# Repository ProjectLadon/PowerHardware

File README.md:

# PowerHardware
Solar panel MPPT/battery charger/power combiner hardware

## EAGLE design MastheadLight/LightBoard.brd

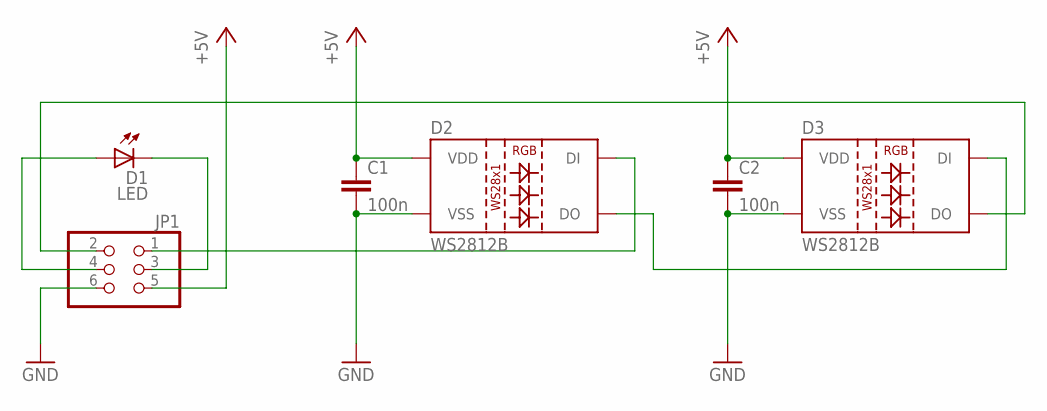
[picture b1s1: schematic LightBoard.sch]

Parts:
C1, C2: 100n; C0603
D1: LED; LM561C
D2, D3: WS2812B
JP1: PINHD-2X3_2.54-SMD-90°; 2X03SMD/90

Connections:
+5V: C1.1, C2.1, D2.1 (VDD), D3.1 (VDD), JP1.5
GND: C1.2, C2.2, D2.3 (VSS), D3.3 (VSS), JP1.6
unnamed: D2.2 (DO), D3.4 (DI)
unnamed: D2.4 (DI), JP1.1
unnamed: D3.2 (DO), JP1.2
unnamed: D1.A1 (A), D1.A2 (A), D1.A3 (A), JP1.4
unnamed: D1.C1 (C), D1.C2 (C), D1.C3 (C), JP1.3

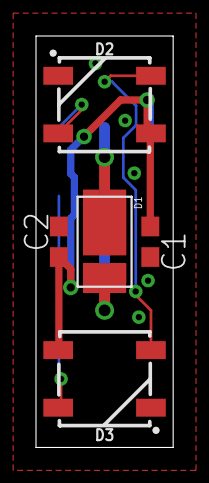
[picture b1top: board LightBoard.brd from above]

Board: 2 copper layers, 7.6 x 22.9 mm, 6 parts (1 on the bottom side), 7 nets.

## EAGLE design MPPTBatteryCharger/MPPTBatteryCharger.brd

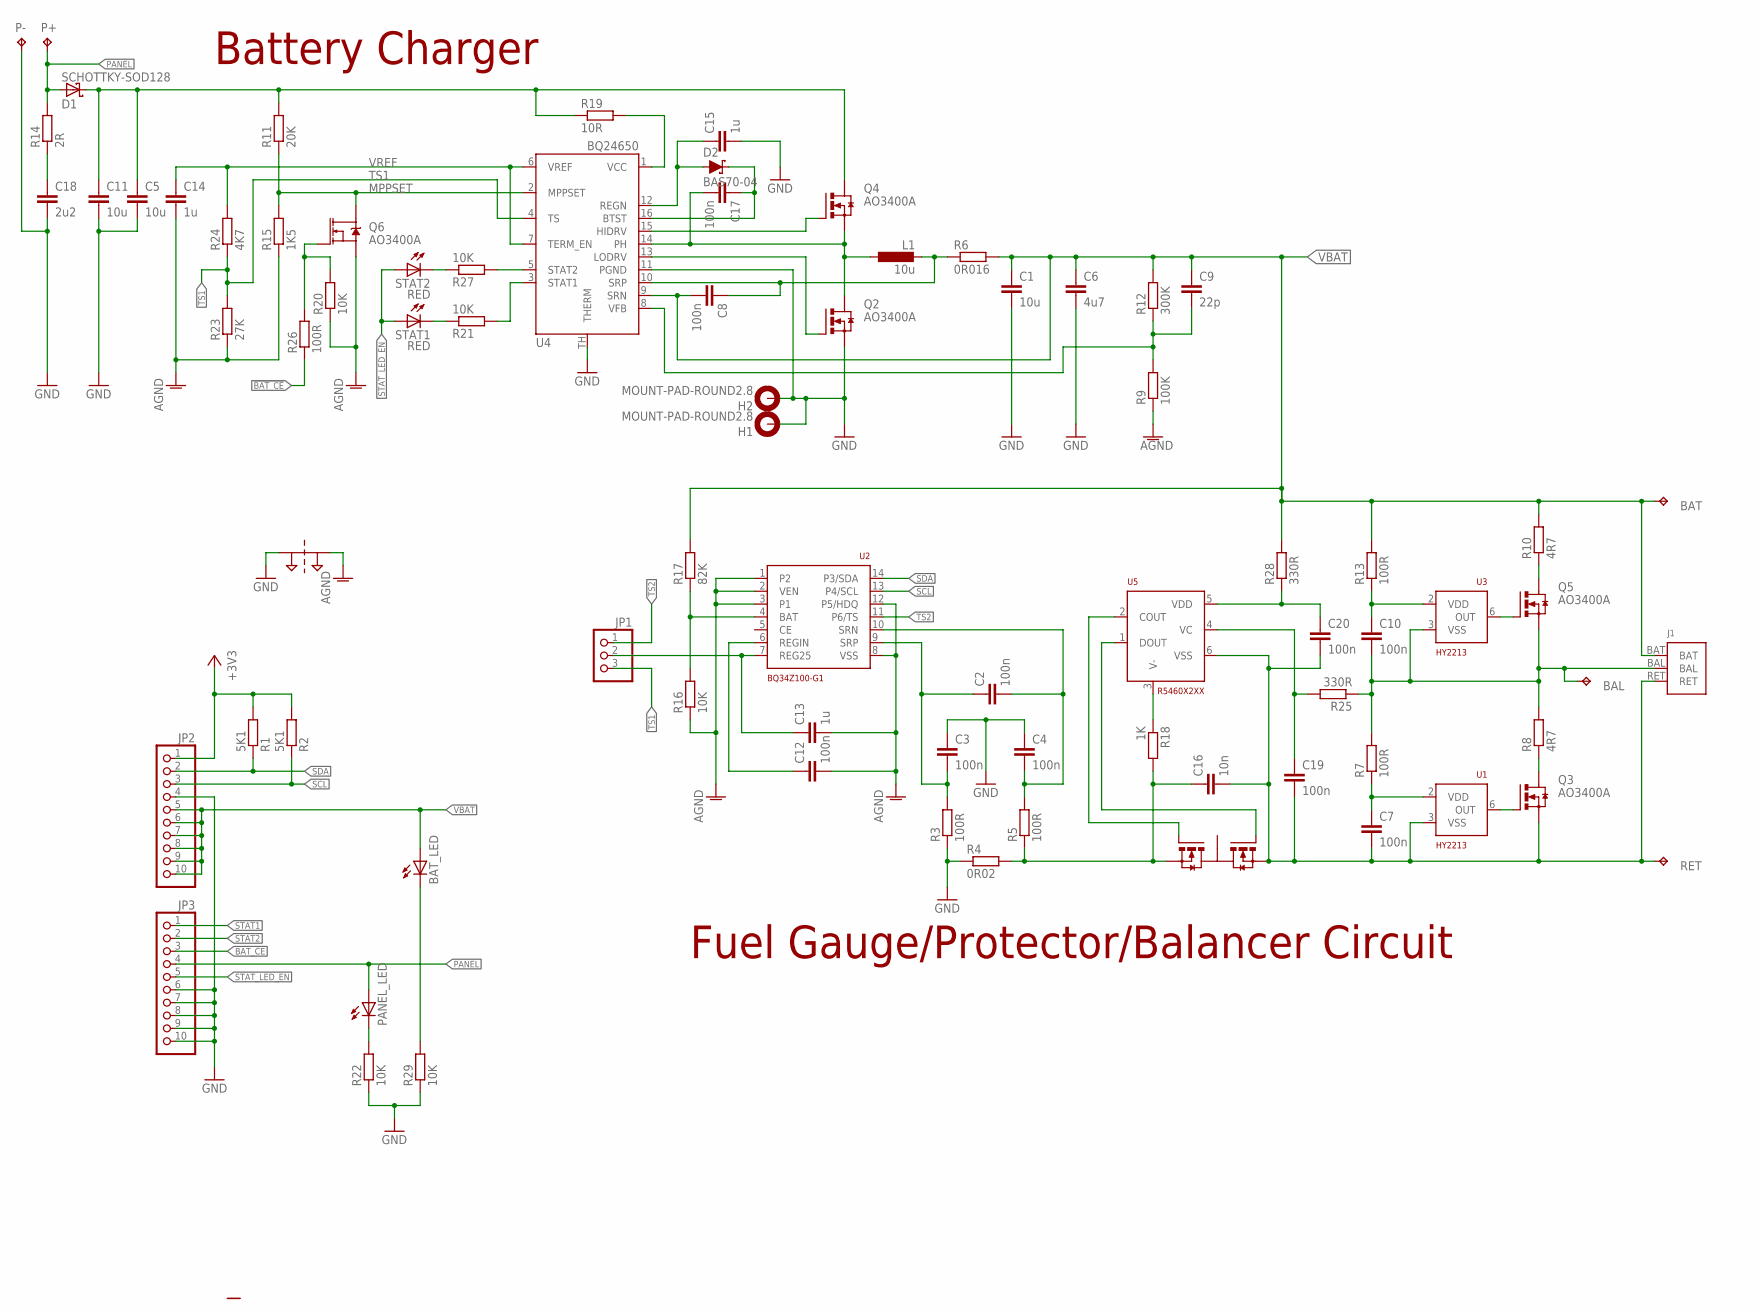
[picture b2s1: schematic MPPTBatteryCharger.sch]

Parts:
BAL: TPPAD1-13Y; P1-13Y
BAT: TPPAD1-13Y; P1-13Y
BAT_LED: LEDCHIP-LED0603; CHIP-LED0603
C1, C5, C11: 10u; C1206
C2, C3, C4, C7, C8, C10, C12, C17, C19, C20: 100n; C0402
C6: 4u7; C1206
C9: 22p; C0402
C13, C14, C15: 1u; C0402
C16: 10n; C0402
C18: 2u2; C0603
D1: SCHOTTKY-SOD128; SOD-128
D2: BAS70-04; SOT23-3
H1, H2: MOUNT-PAD-ROUND2.8; 2,8-PAD
J1: 2S-BATTERYSMD; JST-XH3-SMD
JP1: PINHD-1X3; 1X03
JP2, JP3: PINHD-1X10; 1X10
L1: 10u; MWSA1205
P+: TPPAD1-13Y; P1-13Y
P-: TPPAD1-13Y; P1-13Y
PANEL_LED: LEDCHIP-LED0603; CHIP-LED0603
Q1: FS8205; SOT23-6L
Q2, Q3, Q4, Q5: AO3400A; SOT23
Q6: AO3400A; SOT23-3
R1, R2: 5K1; R0402
R3, R5, R7, R13, R26: 100R; R0402
R4: 0R02; R1206
R6: 0R016; R1206
R8, R10: 4R7; R1206
R9: 100K; R0402
R11: 20K; R0402
R12: 300K; R0402
R14: 2R; R1206
R15: 1K5; R0402
R16: 10K; R0603
R17: 82K; R0603
R18: 1K; R0402
R19: 10R; R0402
R20, R21, R22, R27, R29: 10K; R0402
R23: 27K; R0402
R24: 4K7; R0402
R25, R28: 330R; R0402
RET: TPPAD1-13Y; P1-13Y
STAT1, STAT2: RED; CHIP-LED0603
SUPPLY1: 2PT_GND_TIE
U1, U3: HY2213; SOT23-6L; MFG_PN HY2213-BB3A; LCSC_PN C113632
U2: BQ34Z100-G1; TSSOP14; MFG_PN BQ34Z100PWR-G1; LCSC_PN C91302
U4: BQ24650; QFN16
U5: R5460X2XX; SOT23-6L; LCSC_PN C259719

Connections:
!BAT_CE!: JP3.3, R26.1
+3V3: JP2.1, R1.2, R2.2
AGND: C12.2, C13.2, C14.2, Q6.2 (S), R9.1, R15.1, R16.1, R20.1, R23.1, SUPPLY1.P$2, U2.1 (P2), U2.2 (VEN), U2.3 (P1), U2.8 (VSS), U2.12 (P5/HDQ)
BAL: BAL.TP, C10.2, J1.BAL, Q5.2 (S), R7.2, R8.2, R25.1, U3.3 (VSS)
GND: C1.2, C3.1, C4.1, C5.2, C6.2, C11.2, C15.2, C18.2, H1.B2,8, H2.B2,8, JP2.4, JP3.6, JP3.7, JP3.8, JP3.9, JP3.10, P-.TP, Q2.2 (S), R3.1, R4.1, R22.1, R29.1, SUPPLY1.P$1, U4.11 (PGND), U4.TH (THERM)
MPPSET: Q6.3 (D), R11.1, R15.2, U4.2 (MPPSET)
unnamed: C18.1, R14.1
unnamed: Q5.1 (G), U3.6 (OUT)
unnamed: R19.2, U4.1 (VCC)
unnamed: C5.1, C11.1, D1.C, Q4.3 (D), R11.2, R19.1
unnamed: Q4.1 (G), U4.15 (HIDRV)
unnamed: C17.2, L1.1, Q2.3 (D), Q4.2 (S), U4.14 (PH)
unnamed: Q2.1 (G), U4.13 (LODRV)
unnamed: Q6.1 (G), R20.2, R26.2
unnamed: C8.1, L1.2, R6.1, U4.10 (SRP)
unnamed: C17.1, D2.3 (C), U4.16 (BTST)
unnamed: C15.1, D2.1 (A), U4.12 (REGN)
unnamed: C9.2, R9.2, R12.1, U4.8 (VFB)
unnamed: Q3.1 (G), U1.6 (OUT)
unnamed: R21.1, STAT1.C
unnamed: Q3.3 (D), R8.1
unnamed: R16.2, R17.1, U2.4 (BAT)
unnamed: Q5.3 (D), R10.1
unnamed: C10.1, R13.1, U3.2 (VDD)
unnamed: C7.1, R7.1, U1.2 (VDD)
unnamed: R18.1, U5.3 (V-)
unnamed: C19.1, R25.2, U5.4 (VC)
unnamed: C20.1, R28.1, U5.5 (VDD)
unnamed: C16.1, Q1.1 (S1), R4.2, R5.1, R18.2
unnamed: Q1.6 (G1), U5.2 (COUT)
unnamed: Q1.4 (G2), U5.1 (DOUT)
unnamed: C2.2, C4.2, R5.2, U2.10 (SRN)
unnamed: C2.1, C3.2, R3.2, U2.9 (SRP)
unnamed: C12.1, U2.6 (REGIN)
unnamed: R27.1, STAT2.C
unnamed: BAT_LED.C, R29.2
unnamed: PANEL_LED.C, R22.2
PANEL: D1.A, JP3.4, P+.TP, PANEL_LED.A, R14.2
REG25: C13.1, JP1.2, U2.7 (REG25)
RET: C7.2, C16.2, C19.2, C20.2, J1.RET, Q1.3 (S2), Q3.2 (S), RET.TP, U1.3 (VSS), U5.6 (VSS)
SCL: JP2.3, R2.1, U2.13 (P4/SCL)
SDA: JP2.2, R1.1, U2.14 (P3/SDA)
STAT1: JP3.1, R21.2, U4.3 (STAT1)
STAT2: JP3.2, R27.2, U4.5 (STAT2)
STAT_LED_EN: JP3.5, STAT1.A, STAT2.A
TS1: JP1.3, R23.2, R24.1, U4.4 (TS)
TS2: JP1.1, U2.11 (P6/TS)
VBAT: BAT.TP, BAT_LED.A, C1.1, C6.1, C8.2, C9.1, J1.BAT, JP2.5, JP2.6, JP2.7, JP2.8, JP2.9, JP2.10, R6.2, R10.2, R12.2, R13.2, R17.2, R28.2, U4.9 (SRN)
VREF: C14.1, R24.2, U4.6 (VREF), U4.7 (TERM_EN)

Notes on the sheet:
Battery Charger
Fuel Gauge/Protector/Balancer Circuit

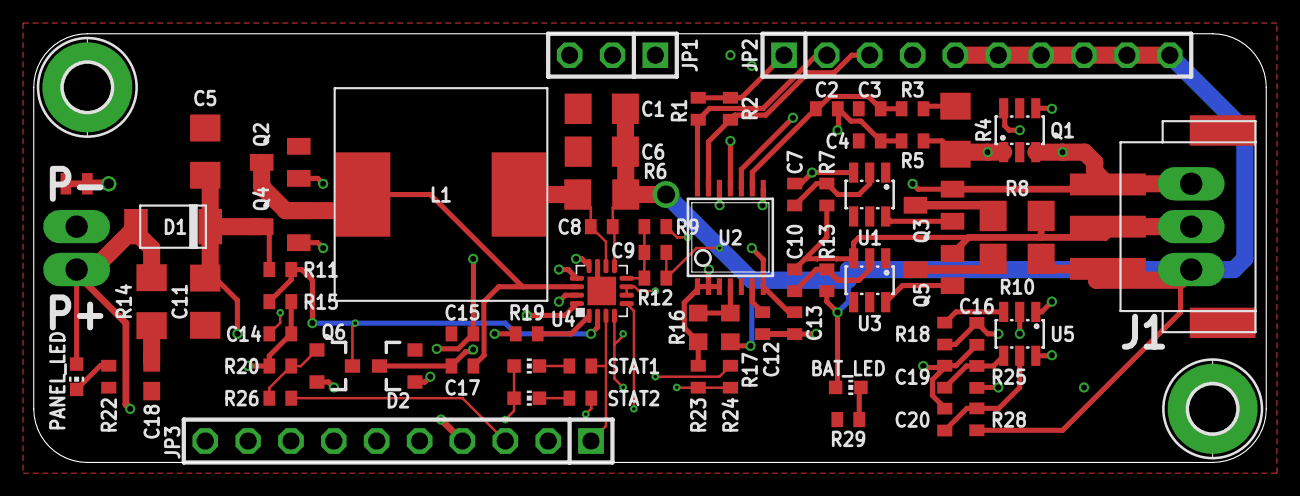
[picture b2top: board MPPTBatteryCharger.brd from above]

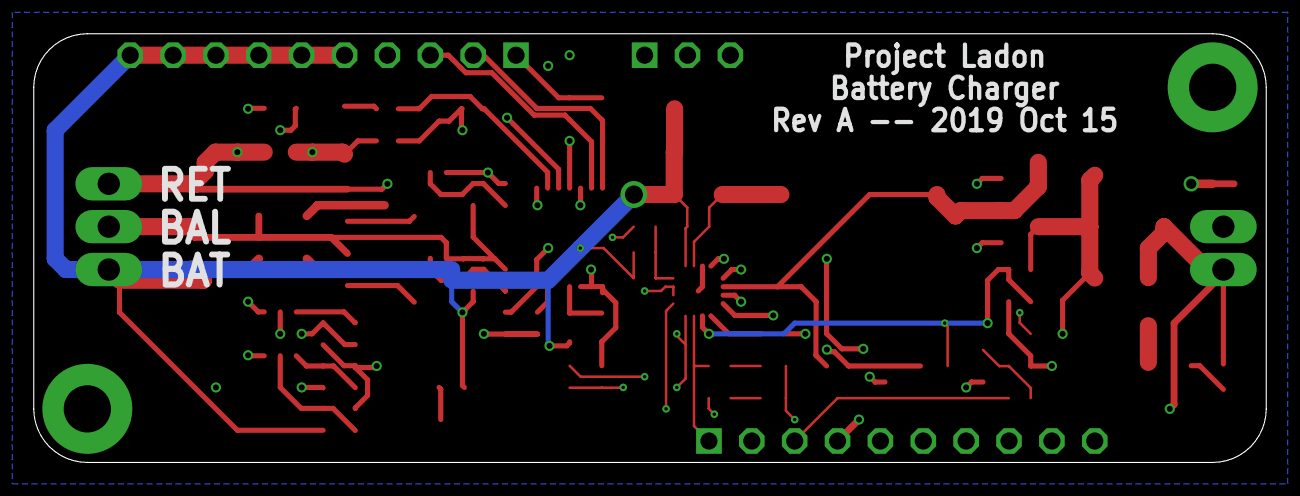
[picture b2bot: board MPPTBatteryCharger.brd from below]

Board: 4 copper layers, 73.0 x 25.4 mm, 79 parts (2 on the bottom side), 49 nets.

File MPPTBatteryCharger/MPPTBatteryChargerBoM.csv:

"Qty";"Value";"Device";"Package";"Parts";"Description";"LCSC_PN";"MFG_PN";"PROD_ID";"TP_SIGNAL_NAME";"VALUE";
"2";"";"LEDCHIP-LED0603";"CHIP-LED0603";"BAT_LED, PANEL_LED";"LED";"";"";"";"";"";
"2";"";"PINHD-1X10";"1X10";"JP2, JP3";"PIN HEADER";"";"";"";"";"";
"1";"";"PINHD-1X3";"1X03";"JP1";"PIN HEADER";"";"";"";"";"";
"1";"0R016";"R-EU_R1206";"R1206";"R6";"RESISTOR, European symbol";"";"";"";"";"";
"1";"0R02";"R-EU_R1206";"R1206";"R4";"RESISTOR, European symbol";"";"";"";"";"";
"1";"100K";"R-EU_R0402";"R0402";"R9";"RESISTOR, European symbol";"";"";"";"";"";
"5";"100R";"R-EU_R0402";"R0402";"R3, R5, R7, R13, R26";"RESISTOR, European symbol";"";"";"";"";"";
"10";"100n";"C-EUC0402";"C0402";"C2, C3, C4, C7, C8, C10, C12, C17, C19, C20";"CAPACITOR, European symbol";"";"";"";"";"";
"5";"10K";"R-EU_R0402";"R0402";"R20, R21, R22, R27, R29";"RESISTOR, European symbol";"";"";"";"";"";
"1";"10K";"R-EU_R0603";"R0603";"R16";"RESISTOR, European symbol";"";"";"";"";"";
"1";"10R";"R-EU_R0402";"R0402";"R19";"RESISTOR, European symbol";"";"";"";"";"";
"1";"10n";"C-EUC0402";"C0402";"C16";"CAPACITOR, European symbol";"";"";"";"";"";
"3";"10u";"C-EUC1206";"C1206";"C1, C5, C11";"CAPACITOR, European symbol";"";"";"";"";"";
"1";"10u";"INDUCTORMWSA1205";"MWSA1205";"L1";"";"";"";"";"";"";
"1";"1K";"R-EU_R0402";"R0402";"R18";"RESISTOR, European symbol";"";"";"";"";"";
"1";"1K5";"R-EU_R0402";"R0402";"R15";"RESISTOR, European symbol";"";"";"";"";"";
"3";"1u";"C-EUC0402";"C0402";"C13, C14, C15";"CAPACITOR, European symbol";"";"";"";"";"";
"1";"20K";"R-EU_R0402";"R0402";"R11";"RESISTOR, European symbol";"";"";"";"";"";
"1";"22p";"C-EUC0402";"C0402";"C9";"CAPACITOR, European symbol";"";"";"";"";"";
"1";"27K";"R-EU_R0402";"R0402";"R23";"RESISTOR, European symbol";"";"";"";"";"";
"1";"2PT_GND_TIE";"2PT_GND_TIE";"2PT_GND_TIE";"SUPPLY1";"Dual Ground Supply";"";"";"";"";"";
"1";"2R";"R-EU_R1206";"R1206";"R14";"RESISTOR, European symbol";"";"";"";"";"";
"1";"2S-BATTERYSMD";"2S-BATTERYSMD";"JST-XH3-SMD";"J1";"JST XH connector for a 2S LiPo battery with balancing";"";"";"";"";"";
"1";"2u2";"C-EUC0603";"C0603";"C18";"CAPACITOR, European symbol";"";"";"";"";"";
"1";"300K";"R-EU_R0402";"R0402";"R12";"RESISTOR, European symbol";"";"";"";"";"";
"2";"330R";"R-EU_R0402";"R0402";"R25, R28";"RESISTOR, European symbol";"";"";"";"";"";
"1";"4K7";"R-EU_R0402";"R0402";"R24";"RESISTOR, European symbol";"";"";"";"";"";
"2";"4R7";"R-EU_R1206";"R1206";"R8, R10";"RESISTOR, European symbol";"";"";"";"";"";
"1";"4u7";"C-EUC1206";"C1206";"C6";"CAPACITOR, European symbol";"";"";"";"";"";
"2";"5K1";"R-EU_R0402";"R0402";"R1, R2";"RESISTOR, European symbol";"";"";"";"";"";
"1";"82K";"R-EU_R0603";"R0603";"R17";"RESISTOR, European symbol";"";"";"";"";"";
"4";"AO3400A";"AO3400A";"SOT23";"Q2, Q3, Q4, Q5";"";"";"";"";"";"";
"1";"AO3400A";"MOSFET-NCH-BSS138";"SOT23-3";"Q6";"N-channel MOSFETs";"";"";"TRANS-00830";"";"220mA/50V/3.5Ω";
"1";"BAS70-04";"DIODE-SCHOTTKY-ZLLS500";"SOT23-3";"D2";"Schottky diode";"";"";"DIO-08411";"";"700mA/40V/533mV";
"1";"BQ24650";"BQ24650";"QFN16";"U4";"TI LiPo charger with MPPT";"";"";"";"";"";
"1";"BQ34Z100-G1";"BQ34Z100-G1";"TSSOP14";"U2";"";"C91302";"BQ34Z100PWR-G1";"";"";"";
"1";"FS8205";"FS8205";"SOT23-6L";"Q1";"";"";"";"";"";"";
"2";"HY2213";"HY2213";"SOT23-6L";"U1, U3";"";"C113632";"HY2213-BB3A";"";"";"";
"2";"MOUNT-PAD-ROUND2.8";"MOUNT-PAD-ROUND2.8";"2,8-PAD";"H1, H2";"MOUNTING PAD, round";"";"";"";"";"";
"1";"R5460X2XX";"R5460X2XX";"SOT23-6L";"U5";"";"C259719";"";"";"";"";
"2";"RED";"LEDCHIP-LED0603";"CHIP-LED0603";"STAT1, STAT2";"LED";"";"";"";"";"";
"1";"SCHOTTKY-SOD128";"SCHOTTKY-SOD128";"SOD-128";"D1";"";"";"";"";"";"";
"5";"TPPAD1-13Y";"TPPAD1-13Y";"P1-13Y";"BAL, BAT, P+, P-, RET";"Test pad";"";"";"";"";"";

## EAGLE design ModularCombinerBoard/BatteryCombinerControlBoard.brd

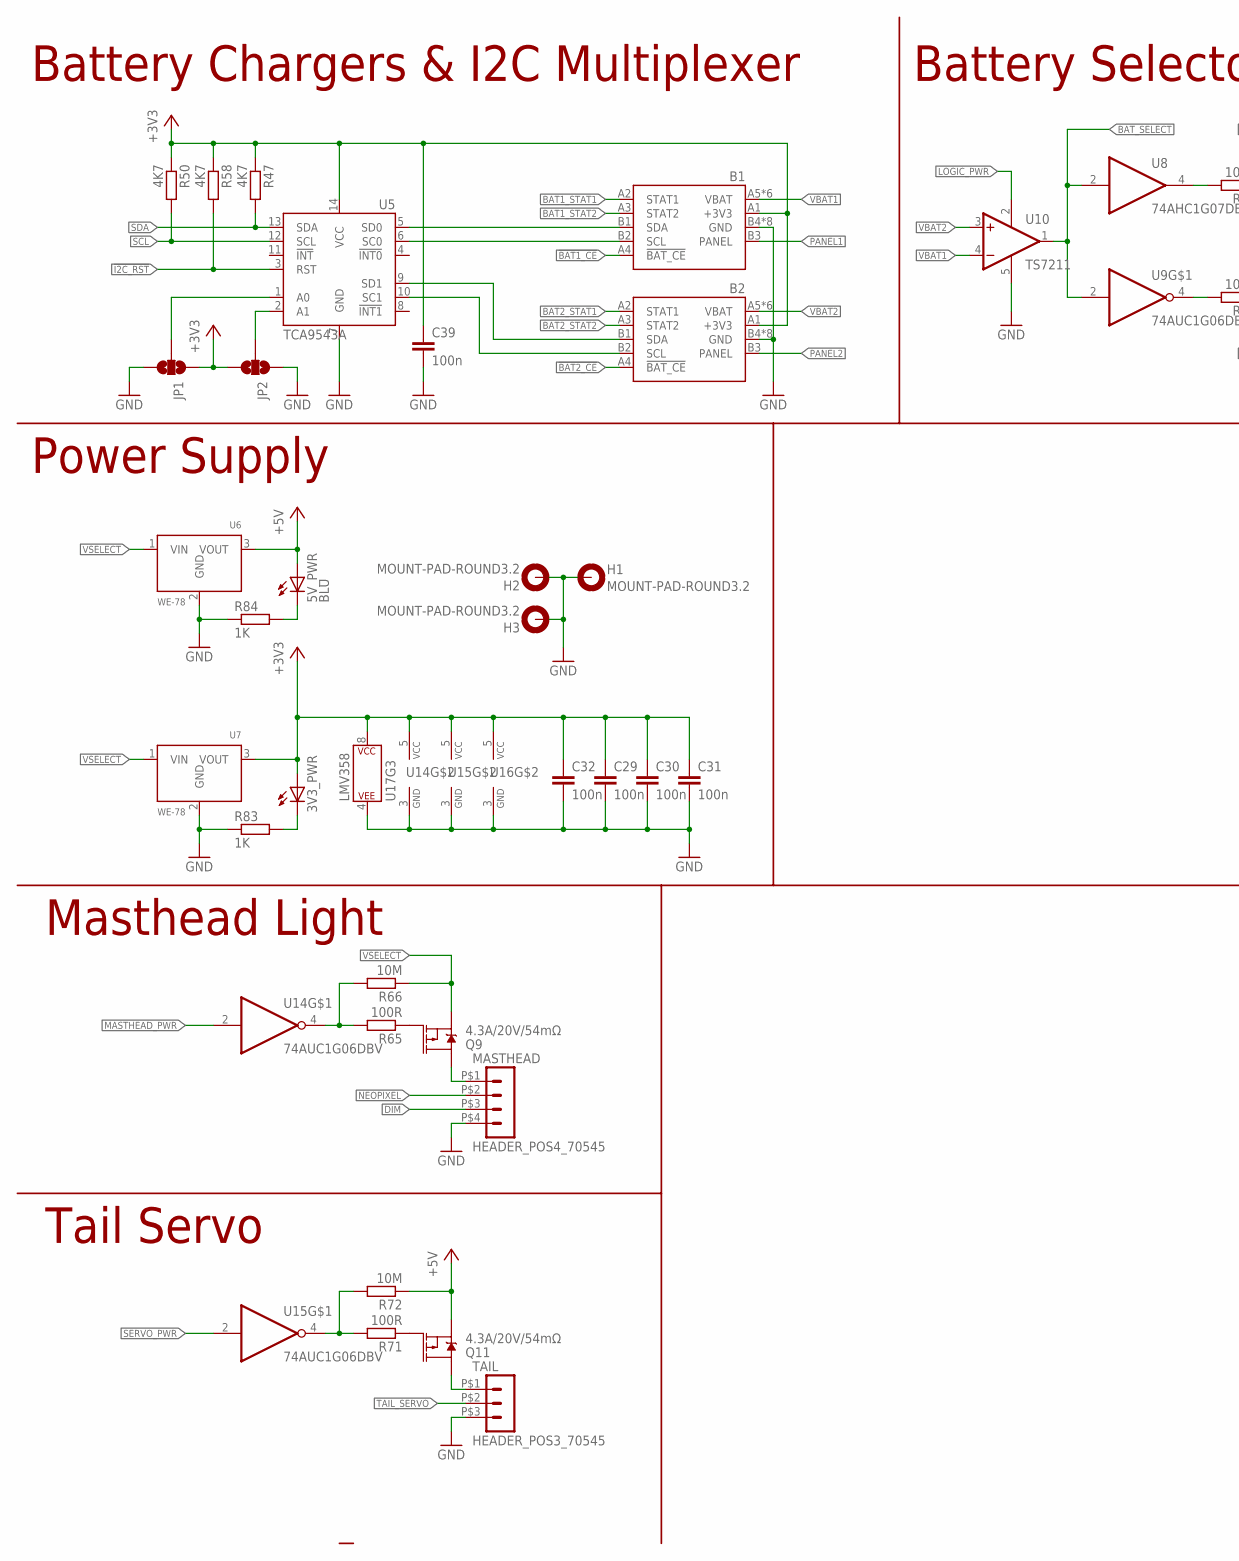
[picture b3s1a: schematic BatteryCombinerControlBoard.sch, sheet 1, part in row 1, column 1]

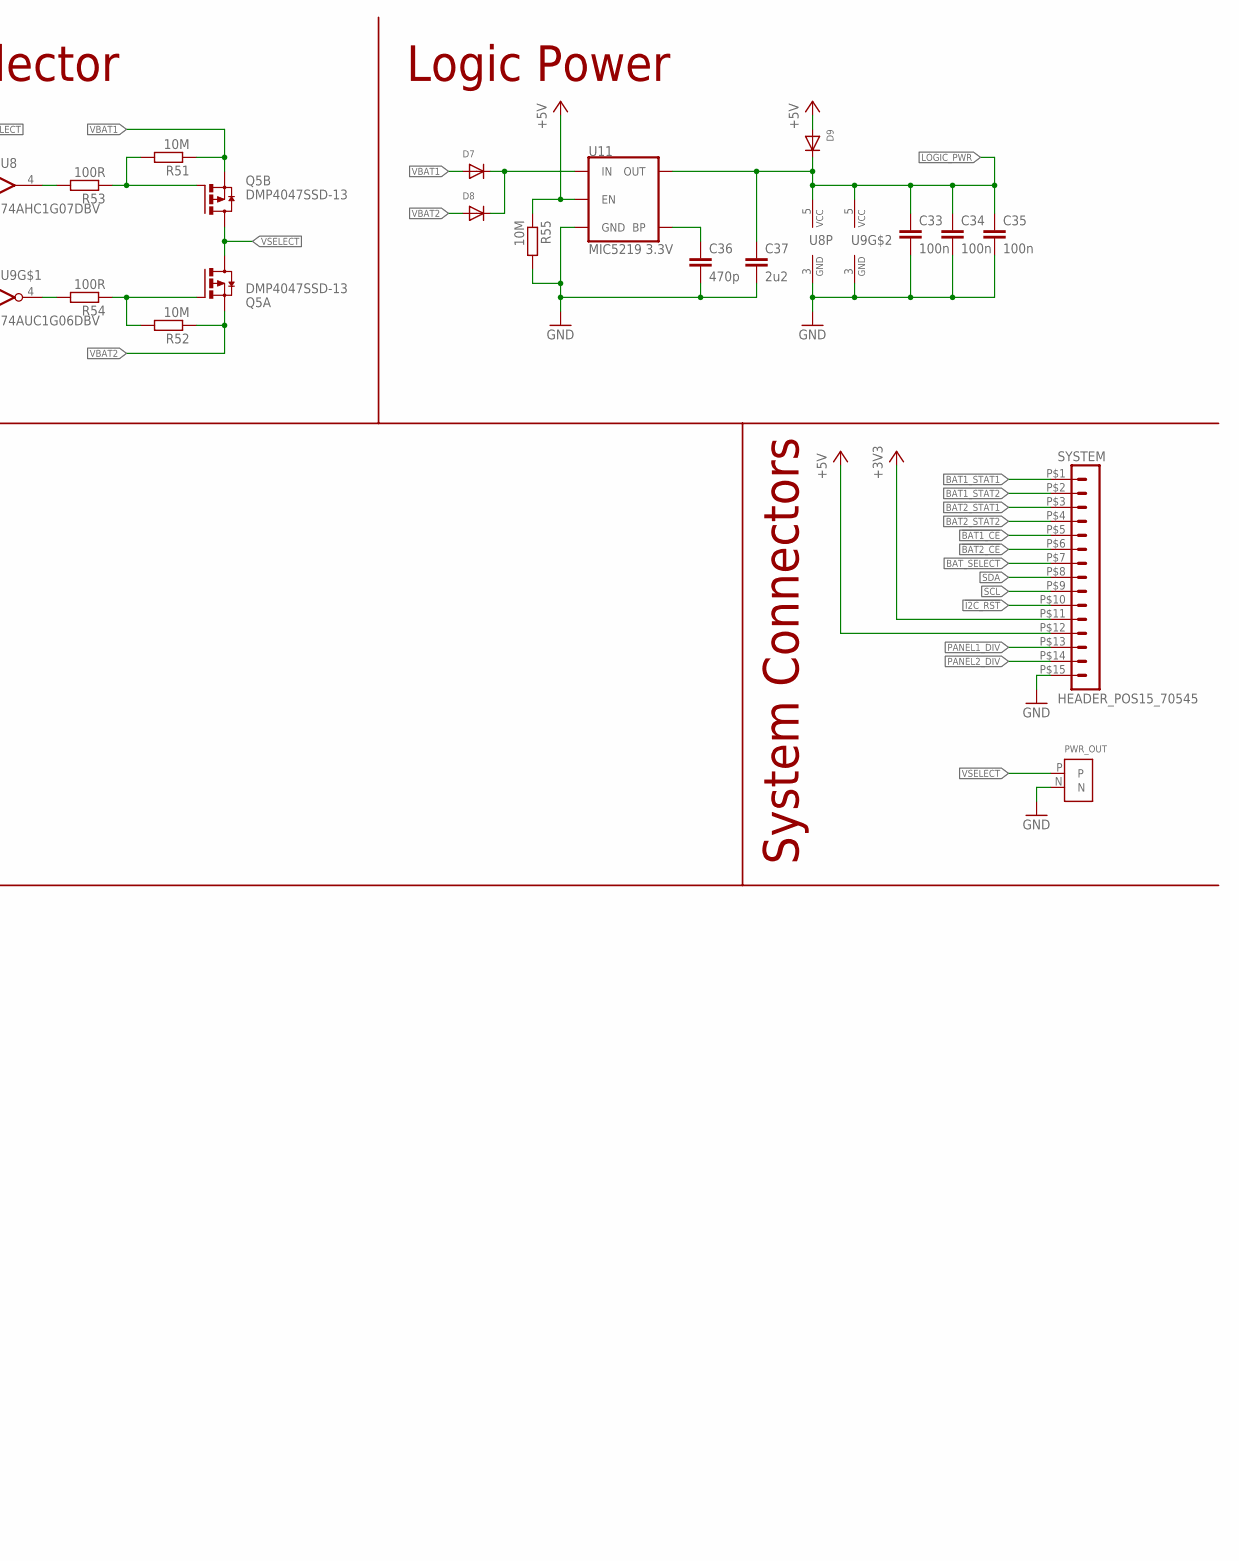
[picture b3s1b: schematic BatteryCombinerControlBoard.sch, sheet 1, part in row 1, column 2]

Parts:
3V3_PWR: GRN; CHIP-LED0603
5V_PWR: BLU; CHIP-LED0603
B1, B2: MPPTCHARGER
C29, C30, C31, C32, C33, C34, C35, C39: 100n; C0603
C36: 470p; C0603
C37: 2u2; C0603
D7, D8, D9: DIODESOD-123; SOD-123
H1, H2, H3: MOUNT-PAD-ROUND3.2; 3,2-PAD
JP1, JP2: JUMPER-SMT_3_NO_SILK; SMT-JUMPER_3_NO_SILK
MASTHEAD: HEADER_POS4_70545; 70545-POS4
PWR_OUT: PWR; JST-XH2-THRUHOLE
Q5: DMP4047SSD-13; SO08
Q9, Q11: 4.3A/20V/54mΩ; SOT23-3
R47, R50, R58: 4K7; R0603
R51, R52, R55, R66, R72: 10M; R0603
R53, R54, R65, R71: 100R; R0603
R83, R84: 1K; R0603
SYSTEM: HEADER_POS15_70545; 70545-POS15
TAIL: HEADER_POS3_70545; 70545-POS3
U5: TCA9543A; SO-14
U6, U7: WE-78
U8: 74AHC1G07DBV; SOT23-5
U9, U14, U15, U16: 74AUC1G06DBV; SOT23-5
U10: TS7211; DBV-R-PDSO-G5
U11: MIC5219 3.3V; SOT23-5
U17: LMV358; SO08

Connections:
!BAT1_CE!: B1.A4 (!BAT_CE!), SYSTEM.P$5 (5); also elsewhere on the board
!BAT2_CE!: B2.A4 (!BAT_CE!), SYSTEM.P$6 (6); also elsewhere on the board
!I2C_RST!: R58.2, SYSTEM.P$10 (10), U5.3 (RST); also elsewhere on the board
+3V3: 3V3_PWR.A, B1.A1 (+3V3), B2.A1 (+3V3), C29.1, C30.1, C31.1, C32.1, C39.1, JP1.1, JP2.3, R47.1, R50.1, R58.1, SYSTEM.P$11 (11), U5.14 (VCC), U7.3 (VOUT), U14.5 (VCC), U15.5 (VCC), U16.5 (VCC), U17.8 (P$V+); also elsewhere on the board
+5V: 5V_PWR.A, D9.A, Q11.2 (S), R55.1, R72.1, SYSTEM.P$12 (12), U6.3 (VOUT), U11.3 (EN); also elsewhere on the board
BAT1_STAT1: B1.A2 (STAT1), SYSTEM.P$1 (1); also elsewhere on the board
BAT1_STAT2: B1.A3 (STAT2), SYSTEM.P$2 (2); also elsewhere on the board
BAT2_STAT1: B2.A2 (STAT1), SYSTEM.P$3 (3); also elsewhere on the board
BAT2_STAT2: B2.A3 (STAT2), SYSTEM.P$4 (4); also elsewhere on the board
BAT_SELECT: SYSTEM.P$7 (7), U8.2 (I), U9.2 (I), U10.1 (OUT); also elsewhere on the board
DIM: MASTHEAD.P$3 (3); also elsewhere on the board
GND: B1.B4 (GND), B1.B5 (GND), B1.B6 (GND), B1.B7 (GND), B1.B8 (GND), B1.B9 (GND), B1.B10 (GND), B1.H (GND), B2.B4 (GND), B2.B5 (GND), B2.B6 (GND), B2.B7 (GND), B2.B8 (GND), B2.B9 (GND), B2.B10 (GND), B2.H (GND), C29.2, C30.2, C31.2, C32.2, C33.2, C34.2, C35.2, C36.2, C37.2, C39.2, H1.B3,2, H2.B3,2, H3.B3,2, JP1.3, JP2.1, MASTHEAD.P$4 (4), PWR_OUT.N, R55.2, R83.1, R84.1, SYSTEM.P$15 (15), TAIL.P$3 (3), U5.7 (GND), U6.2 (GND), U7.2 (GND), U8.3 (GND), U9.3 (GND), U10.5 (GND), U11.2 (GND), U14.3 (GND), U15.3 (GND), U16.3 (GND), U17.4 (P$V-); also elsewhere on the board
LOGIC_PWR: C33.1, C34.1, C35.1, C37.1, D9.C, U8.5 (VCC), U9.5 (VCC), U10.2 (V+), U11.5 (OUT)
MASTHEAD_PWR: U14.2 (I); also elsewhere on the board
unnamed: Q5.4 (G), R51.2, R53.1
unnamed: JP1.2, U5.1 (A0)
unnamed: JP2.2, U5.2 (A1)
unnamed: Q5.2 (G), R52.2, R54.1
unnamed: R54.2, U9.4 (O)
unnamed: R53.2, U8.4 (O)
unnamed: D7.C, D8.C, U11.1 (IN)
unnamed: MASTHEAD.P$1 (1), Q9.3 (D)
unnamed: C36.1, U11.4 (BP)
unnamed: Q9.1 (G), R65.1
unnamed: R65.2, R66.2, U14.4 (O)
unnamed: Q11.3 (D), TAIL.P$1 (1)
unnamed: Q11.1 (G), R71.1
unnamed: R71.2, R72.2, U15.4 (O)
unnamed: 3V3_PWR.C, R83.2
unnamed: 5V_PWR.C, R84.2
NEOPIXEL: MASTHEAD.P$2 (2); also elsewhere on the board
PANEL1: B1.B3 (PANEL); also elsewhere on the board
PANEL1_DIV: SYSTEM.P$13 (13); also elsewhere on the board
PANEL2: B2.B3 (PANEL); also elsewhere on the board
PANEL2_DIV: SYSTEM.P$14 (14); also elsewhere on the board
SCL: R50.2, SYSTEM.P$9 (9), U5.12 (SCL); also elsewhere on the board
SCL1: B1.B2 (SCL), U5.6 (SC0)
SCL2: B2.B2 (SCL), U5.10 (SC1)
SDA: R47.2, SYSTEM.P$8 (8), U5.13 (SDA); also elsewhere on the board
SDA1: B1.B1 (SDA), U5.5 (SD0)
SDA2: B2.B1 (SDA), U5.9 (SD1)
SERVO_PWR: U15.2 (I); also elsewhere on the board
TAIL_SERVO: TAIL.P$2 (2); also elsewhere on the board
VBAT1: B1.A5 (VBAT), B1.A6 (VBAT), B1.A7 (VBAT), B1.A8 (VBAT), B1.A9 (VBAT), B1.A10 (VBAT), D7.A, Q5.3 (S), R51.1, U10.4 (-IN)
VBAT2: B2.A5 (VBAT), B2.A6 (VBAT), B2.A7 (VBAT), B2.A8 (VBAT), B2.A9 (VBAT), B2.A10 (VBAT), D8.A, Q5.1 (S), R52.1, U10.3 (+IN)
VSELECT: PWR_OUT.P, Q5.5 (D), Q5.6 (D), Q5.7 (D), Q5.8 (D), Q9.2 (S), R66.1, U6.1 (VIN), U7.1 (VIN); also elsewhere on the board

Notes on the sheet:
Battery Chargers & I2C Multiplexer
Battery Selector
System Connectors
Logic Power
Power Supply
Masthead Light
Tail Servo

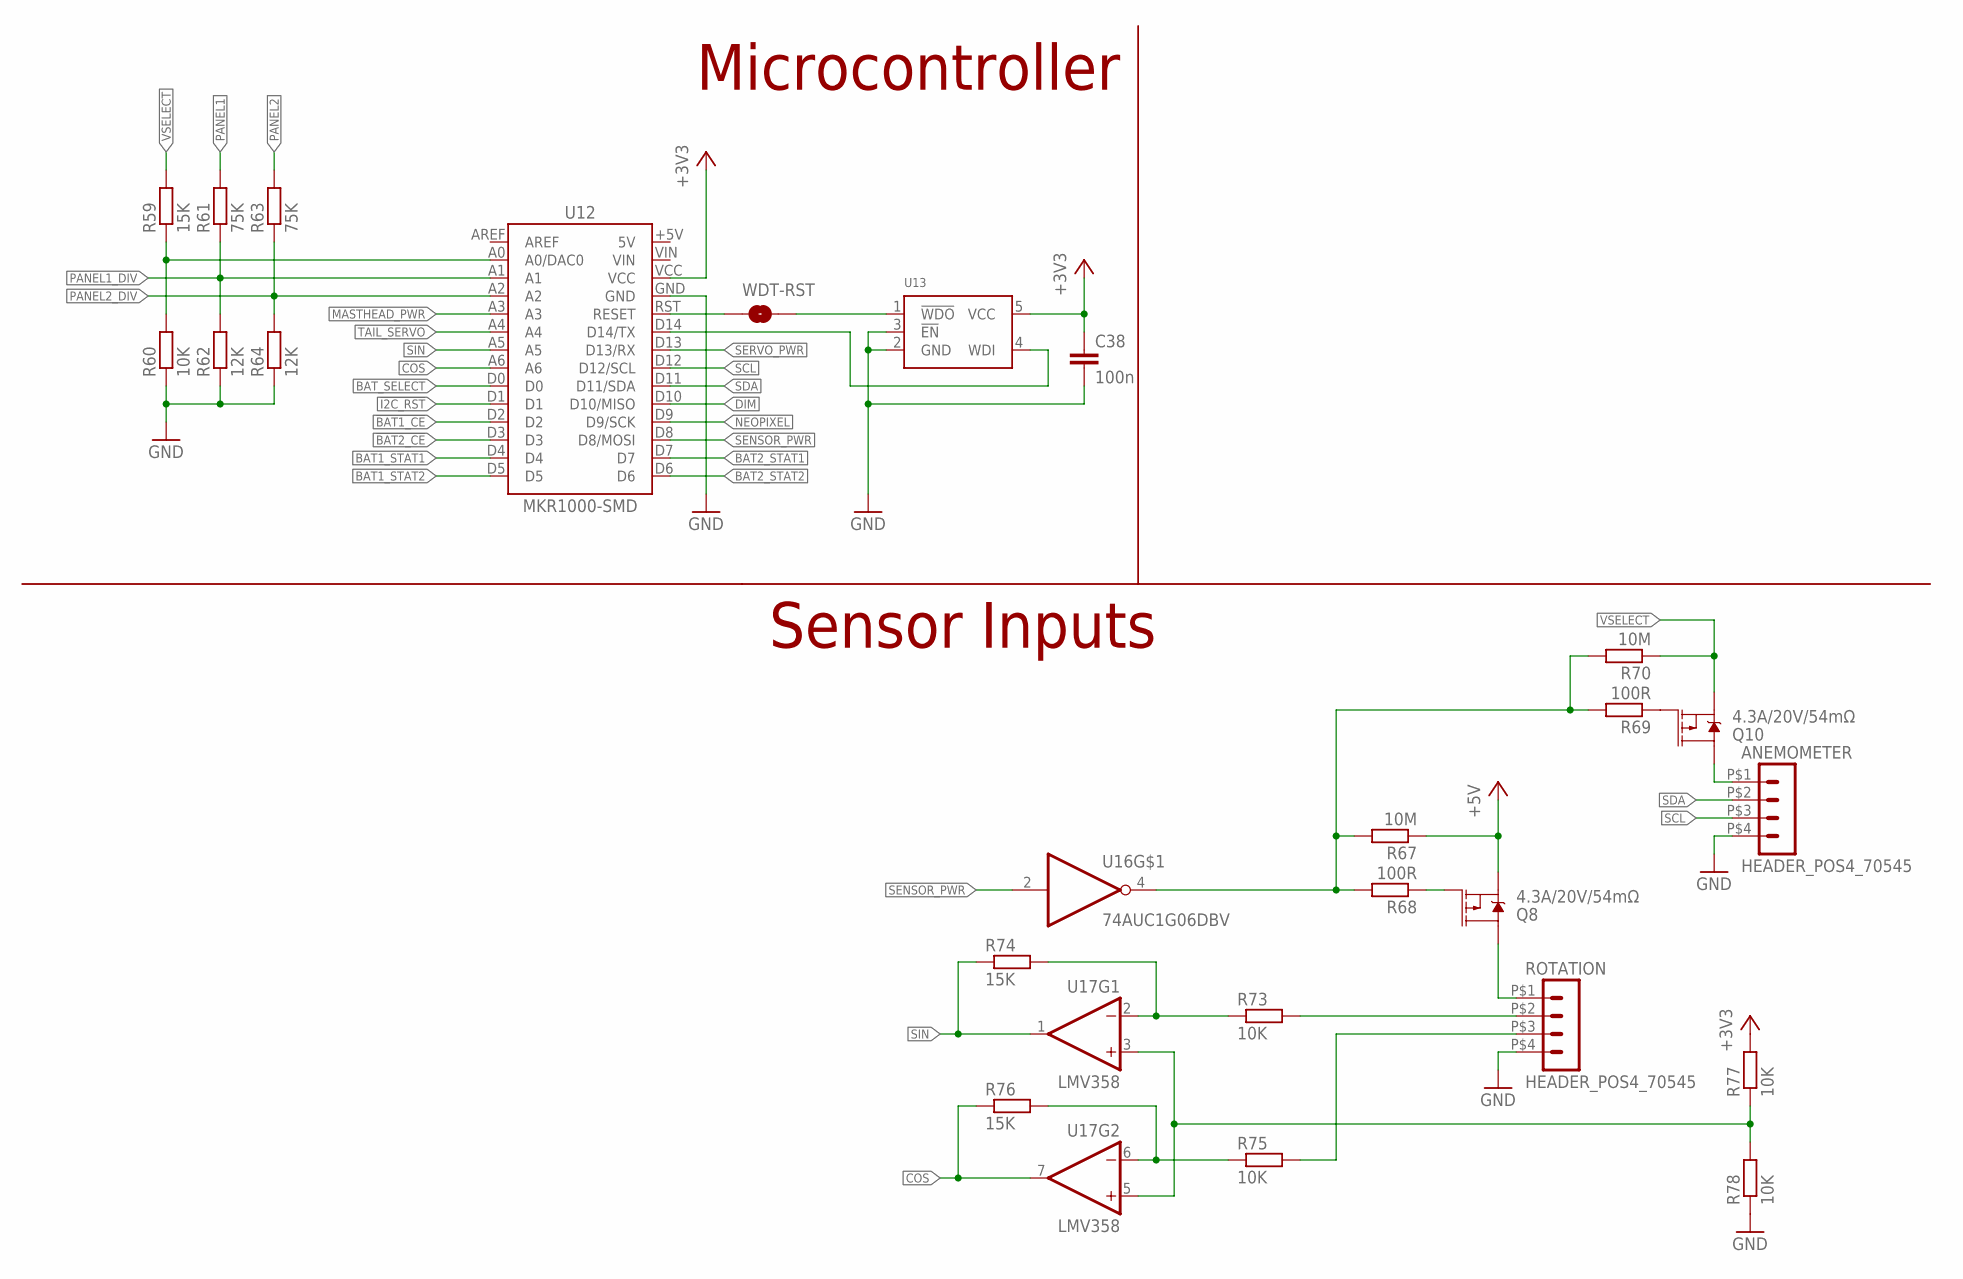
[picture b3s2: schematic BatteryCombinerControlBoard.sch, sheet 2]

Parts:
ANEMOMETER: HEADER_POS4_70545; 70545-POS4
C38: 100n; C0603
Q8, Q10: 4.3A/20V/54mΩ; SOT23-3
R59, R74, R76: 15K; R0603
R60, R73, R75, R77, R78: 10K; R0603
R61, R63: 75K; R0603
R62, R64: 12K; R0603
R67, R70: 10M; R0603
R68, R69: 100R; R0603
ROTATION: HEADER_POS4_70545; 70545-POS4
U12: MKR1000-SMD
U13: STWD100; DBV-R-PDSO-G5
U16: 74AUC1G06DBV; SOT23-5
U17: LMV358; SO08
WDT-RST: JUMPER-SMT_2_NO_SILK; SMT-JUMPER_2_NO_SILK

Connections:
!BAT1_CE!: U12.D2; also elsewhere on the board
!BAT2_CE!: U12.D3; also elsewhere on the board
!I2C_RST!: U12.D1; also elsewhere on the board
+3V3: C38.1, R77.2, U12.VCC, U13.5 (VCC); also elsewhere on the board
+5V: Q8.2 (S), R67.1; also elsewhere on the board
BAT1_STAT1: U12.D4; also elsewhere on the board
BAT1_STAT2: U12.D5; also elsewhere on the board
BAT2_STAT1: U12.D7; also elsewhere on the board
BAT2_STAT2: U12.D6; also elsewhere on the board
BAT_SELECT: U12.D0; also elsewhere on the board
COS: R76.1, U12.A6, U17.7 (OUT)
COS_IN: R75.2, ROTATION.P$3 (3)
DIM: U12.D10 (D10/MISO); also elsewhere on the board
GND: ANEMOMETER.P$4 (4), C38.2, R60.1, R62.1, R64.1, R78.1, ROTATION.P$4 (4), U12.GND, U13.2 (GND), U13.3 (!EN!); also elsewhere on the board
MASTHEAD_PWR: U12.A3; also elsewhere on the board
unnamed: Q8.3 (D), ROTATION.P$1 (1)
unnamed: Q8.1 (G), R68.1
unnamed: R59.1, R60.2, U12.A0 (A0/DAC0)
unnamed: U12.RST (RESET), WDT-RST.1
unnamed: R73.1, R74.2, U17.2 (-IN)
unnamed: U13.1 (!WDO!), WDT-RST.2
unnamed: ANEMOMETER.P$1 (1), Q10.3 (D)
unnamed: Q10.1 (G), R69.1
unnamed: U12.D14 (D14/TX), U13.4 (WDI)
unnamed: R67.2, R68.2, R69.2, R70.2, U16.4 (O)
unnamed: R75.1, R76.2, U17.6 (-IN)
unnamed: R77.1, R78.2, U17.3 (+IN), U17.5 (+IN)
NEOPIXEL: U12.D9 (D9/SCK); also elsewhere on the board
PANEL1: R61.2; also elsewhere on the board
PANEL1_DIV: R61.1, R62.2, U12.A1; also elsewhere on the board
PANEL2: R63.2; also elsewhere on the board
PANEL2_DIV: R63.1, R64.2, U12.A2; also elsewhere on the board
SCL: ANEMOMETER.P$3 (3), U12.D12 (D12/SCL); also elsewhere on the board
SDA: ANEMOMETER.P$2 (2), U12.D11 (D11/SDA); also elsewhere on the board
SENSOR_PWR: U12.D8 (D8/MOSI), U16.2 (I)
SERVO_PWR: U12.D13 (D13/RX); also elsewhere on the board
SIN: R74.1, U12.A5, U17.1 (OUT)
SIN_IN: R73.2, ROTATION.P$2 (2)
TAIL_SERVO: U12.A4; also elsewhere on the board
VSELECT: Q10.2 (S), R59.2, R70.1; also elsewhere on the board

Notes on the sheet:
Microcontroller
Sensor Inputs

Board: 2 copper layers, 78 parts (2 on the bottom side), 63 nets, no tracks yet.

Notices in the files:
parts and their libraries:
SparkFun-Jumpers: Licensing: Creative Commons ShareAlike 4.0 International - https://creativecommons.org/licenses/by-sa/4.0
